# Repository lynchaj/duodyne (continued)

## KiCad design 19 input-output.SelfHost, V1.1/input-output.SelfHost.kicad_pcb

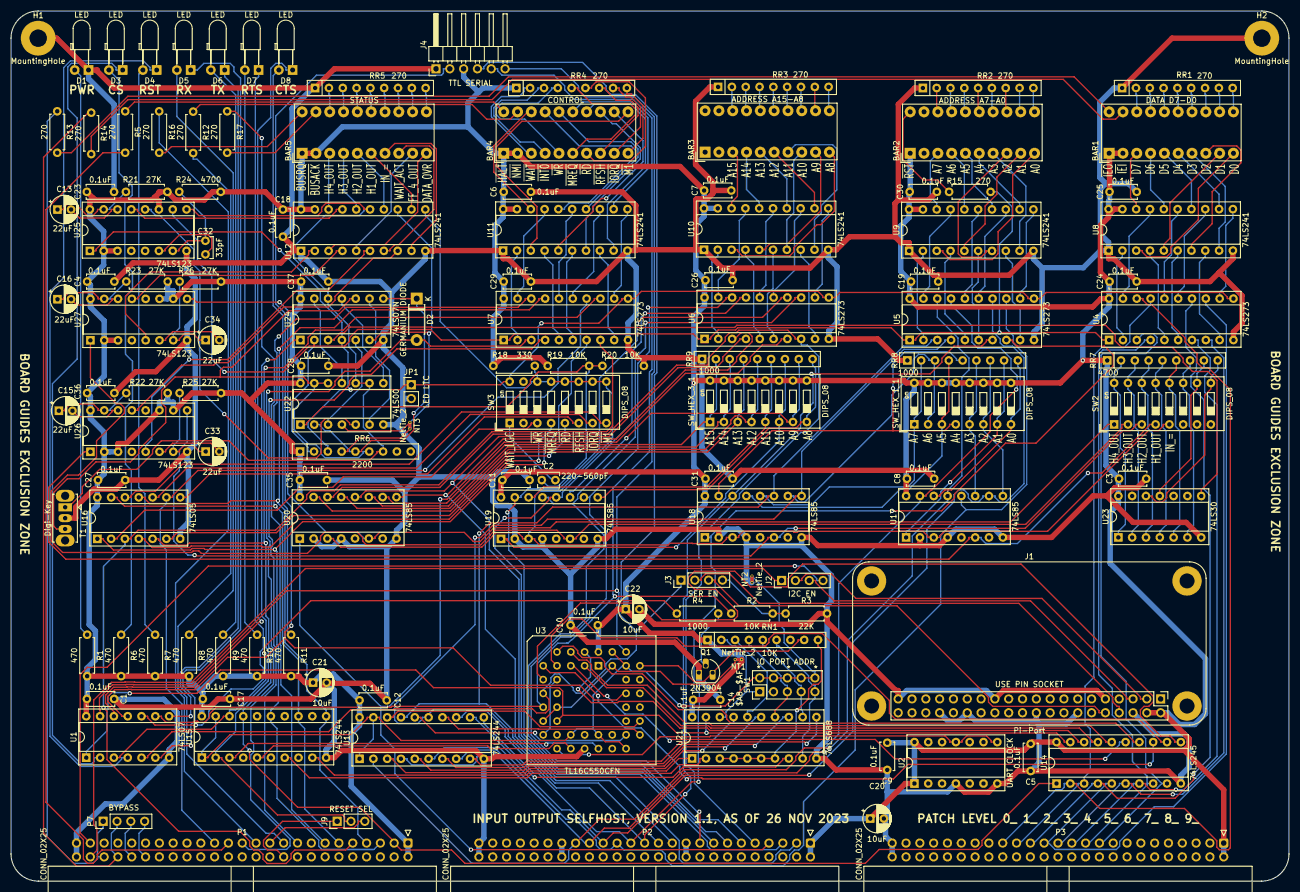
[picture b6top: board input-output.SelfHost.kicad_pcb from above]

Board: 2 copper layers, 235.0 x 160.0 mm, 135 parts (0 on the bottom side), 291 nets.

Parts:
BAR1: DATA D7-D0; HDSP-48xx
BAR2: ADDRESS A7-A0; HDSP-48xx
BAR3: ADDRESS A15-A8; HDSP-48xx
BAR4: CONTROL; HDSP-48xx
BAR5: STATUS; HDSP-48xx
C1, C3, C4, C5, C6, C7, C8, C9, C10, C11, C12, C14, C17, C18, C19, C23, C24, C25, C26, C27, C28, C29, C30, C31, C35, C36, C37: 0.1uF; C_Disc_D5.0mm_W2.5mm_P5.00mm
C2: 220-560pF; C_Disc_D3.8mm_W2.6mm_P2.50mm
C13, C15, C16, C33, C34: 22uF; CP_Radial_D5.0mm_P2.50mm
C20, C21, C22: 10uF; CP_Radial_D5.0mm_P2.50mm
C32: 33pF; C_Disc_D3.8mm_W2.6mm_P2.50mm
D1, D3, D4, D5, D6, D7, D8: LED; LED_D3.0mm_Horizontal_O3.81mm_Z2.0mm
D2: GERMANIUM DIODE; D_DO-41_SOD81_P7.62mm_Horizontal
H1, H2: MountingHole; MountingHole_3.2mm_M3_Pad
J1: Pi-Port
J2: I2C EN; PinHeader_1x04_P2.54mm_Vertical
J3: SER EN; PinHeader_1x04_P2.54mm_Vertical
J4: TTL SERIAL; PinHeader_1x06_P2.54mm_Horizontal
J9: RESET SEL; PinHeader_1x03_P2.54mm_Vertical
JP1: LED LTC; PinHeader_1x02_P2.54mm_Vertical
NT1, NT2, NT3: NetTie_2; NetTie-2_THT_Pad0.3mm
P1, P2, P3: CONN_02X25; IDC-Header_2x25_P2.54mm_Horizontal
P7: BYPASS; PinHeader_1x04_P2.54mm_Vertical
Q1: 2N3904; TO-92_HandSolder
R1, R6, R7, R8, R9, R10, R11: 470; R_Axial_DIN0207_L6.3mm_D2.5mm_P7.62mm_Horizontal
R2, R19, R20: 10K; R_Axial_DIN0207_L6.3mm_D2.5mm_P7.62mm_Horizontal
R3: 22K; R_Axial_DIN0207_L6.3mm_D2.5mm_P7.62mm_Horizontal
R4: 1000; R_Axial_DIN0207_L6.3mm_D2.5mm_P7.62mm_Horizontal
R5, R12, R13, R14, R15, R16, R17: 270; R_Axial_DIN0207_L6.3mm_D2.5mm_P7.62mm_Horizontal
R18: 330; R_Axial_DIN0207_L6.3mm_D2.5mm_P7.62mm_Horizontal
R21, R22, R23, R25, R26: 27K; R_Axial_DIN0207_L6.3mm_D2.5mm_P7.62mm_Horizontal
R24: 4700; R_Axial_DIN0207_L6.3mm_D2.5mm_P7.62mm_Horizontal
RN1: 10K; R_Array_SIP9
RR1, RR2, RR3, RR4, RR5: 270; R_Array_SIP9
RR6: 2200; R_Array_SIP9
RR7: 4700; R_Array_SIP9
RR8, RR9: 1000; R_Array_SIP9
SW1: IO PORT ADDR; PinHeader_2x05_P2.54mm_Vertical
SW2, SW3: DIPS_08; SW_DIP_SPSTx08_Slide_9.78x22.5mm_W7.62mm_P2.54mm
SW_HEX_1_1, SW_HEX_3_1: DIPS_08; SW_DIP_SPSTx08_Slide_9.78x22.5mm_W7.62mm_P2.54mm
T1: Digi-Key; SW_Slide_1P2T_CK_OS102011MS2Q
U1: 74LS07; DIP-14_W7.62mm_Socket
U2: UART CLOCK; DIP-14_W7.62mm_Socket
U3: TL16C550CFN; PLCC-44_THT-Socket
U4, U5, U6, U7: 74LS273; DIP-20_W7.62mm_Socket
U8, U9, U10, U11, U12: 74LS241; DIP-20_W7.62mm_Socket
U13, U15: 74LS244; DIP-20_W7.62mm_Socket
U14: 74LS245; DIP-20_W7.62mm_Socket
U16: 74LS05; DIP-14_W7.62mm_Socket
U17, U18, U19, U20: 74LS85; DIP-16_W7.62mm_Socket
U21: 74LS688; DIP-20_W7.62mm_Socket
U22: 74LS00; DIP-14_W7.62mm_Socket
U23: 74LS30; DIP-14_W7.62mm_Socket
U24: 74LS07N; DIP-14_W7.62mm_Socket
U25, U26, U27: 74LS123; DIP-16_W7.62mm_Socket

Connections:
+12V: P2.19, P2.20
-12V: P2.37, P2.38
/BusMonitor/DATA_OVER: U12.17 (I3b), U25.13 (Q)
/BusMonitor/FF_1_OUT: NT3.2, RR6.4 (R3)
/BusMonitor/FF_2_OUT: D2.1 (K), RR6.5 (R4), U22.2, U24.8
/BusMonitor/FF_3_OUT: RR6.6 (R5), T1.3 (C), U22.12, U22.13, U24.10
/BusMonitor/FF_4_OUT: RR6.7 (R6), T1.1 (A), U12.15 (I2b), U22.9, U22.10, U24.12, U25.9 (A)
/BusMonitor/H1_LED: U12.8 (I3a), U26.13 (Q)
/BusMonitor/H1_OUT_=: SW2.4, U17.6 (Oa=b), U26.1 (A)
/BusMonitor/H2_LED: U12.6 (I2a), U26.5 (Q)
/BusMonitor/H2_OUT_=: SW2.3, U18.6 (Oa=b), U26.9 (A)
/BusMonitor/H3_LED: U12.4 (I1a), U27.13 (Q)
/BusMonitor/H3_OUT_=: SW2.2, U19.6 (Oa=b), U27.1 (A)
/BusMonitor/H4_LED: U12.2 (I0a), U27.5 (Q)
/BusMonitor/H4_OUT_=: SW2.1, U20.6 (Oa=b), U27.9 (A)
/BusMonitor/H_A0: RR8.9 (R8), SW_HEX_1_1.8, U17.14 (B2)
/BusMonitor/H_A1: RR8.8 (R7), SW_HEX_1_1.7, U17.1 (B3)
/BusMonitor/H_A2: RR8.7 (R6), SW_HEX_1_1.6, U17.9 (B0)
/BusMonitor/H_A3: RR8.6 (R5), SW_HEX_1_1.5, U17.11 (B1)
/BusMonitor/H_A4: RR8.5 (R4), SW_HEX_1_1.4, U18.15 (A3)
/BusMonitor/H_A5: RR8.4 (R3), SW_HEX_1_1.3, U18.13 (A2)
/BusMonitor/H_A6: RR8.3 (R2), SW_HEX_1_1.2, U18.10 (A0)
/BusMonitor/H_A7: RR8.2 (R1), SW_HEX_1_1.1, U18.12 (A1)
/BusMonitor/H_A8: RR9.9 (R8), SW_HEX_3_1.8, U19.9 (B0)
/BusMonitor/H_A9: RR9.8 (R7), SW_HEX_3_1.7, U19.11 (B1)
/BusMonitor/H_A10: RR9.7 (R6), SW_HEX_3_1.6, U19.1 (B3)
/BusMonitor/H_A11: RR9.6 (R5), SW_HEX_3_1.5, U19.14 (B2)
/BusMonitor/H_A12: RR9.5 (R4), SW_HEX_3_1.4, U20.13 (A2)
/BusMonitor/H_A13: RR9.4 (R3), SW_HEX_3_1.3, U20.15 (A3)
/BusMonitor/H_A14: RR9.3 (R2), SW_HEX_3_1.2, U20.11 (B1)
/BusMonitor/H_A15: RR9.2 (R1), SW_HEX_3_1.1, U20.10 (A0)
/BusMonitor/IN_=: R18.2, SW2.5, SW3.9, SW3.10, SW3.11, SW3.12, SW3.13, SW3.14, U12.11 (I0b), U17.3 (Ia=b), U18.3 (Ia=b), U19.3 (Ia=b), U20.3 (Ia=b)
/BusMonitor/LED_LATCH: JP1.1 (A), RR6.3 (R2), SW3.16, U4.11 (Cp), U5.11 (Cp), U6.11 (Cp), U7.11 (Cp), U24.4, U25.1 (A)
/BusMonitor/MAS_RESET: R15.2, RR6.2 (R1), U4.1 (~Mr), U5.1 (~Mr), U6.1 (~Mr), U7.1 (~Mr), U24.2, U25.10 (B)
/BusMonitor/S2_1: RR7.2 (R1), SW2.16, U23.1
/BusMonitor/S2_2: RR7.3 (R2), SW2.15, U23.2
/BusMonitor/S2_3: RR7.4 (R3), SW2.14, U23.3
/BusMonitor/S2_4: RR7.5 (R4), SW2.13, U23.4
/BusMonitor/S2_5: RR7.6 (R5), SW2.12, U23.5
/BusMonitor/S2_6: RR7.7 (R6), SW2.11, U23.6
/BusMonitor/S2_7: RR7.8 (R7), SW2.10, U23.11
/BusMonitor/S2_8: RR7.9 (R8), SW2.9, U23.12
/BusMonitor/WAIT_ACTIVE: NT3.1, U12.13 (I1b), U22.4, U24.6
/BusMonitor/WAIT_FF: U22.5, U25.12 (~Q)
/BusMonitor/WAIT_LOGIC: C2.1, R19.2, R20.1, U22.1
A0: P2.35, U5.18 (D7), U13.2 (I0a), U17.13 (A2)
A1: P2.33, U5.17 (D6), U13.4 (I1a), U17.15 (A3)
A2: P2.31, U5.14 (D5), U13.6 (I2a), U17.10 (A0)
A3: P2.29, U5.13 (D4), U13.8 (I3a), U17.12 (A1)
A4: P2.27, U5.8 (D3), U13.11 (I0b), U18.1 (B3)
A5: P2.25, U5.7 (D2), U13.13 (I1b), U18.14 (B2)
A6: P2.23, U5.4 (D1), U13.15 (I2b), U18.9 (B0)
A7: P2.21, U5.3 (D0), U13.17 (I3b), U18.11 (B1)
A8: P2.17, U6.18 (D7), U19.10 (A0)
A9: P2.15, U6.17 (D6), U19.12 (A1)
A10: P2.13, U6.14 (D5), U19.15 (A3)
A11: P2.11, U6.13 (D4), U19.13 (A2)
A12: P2.9, U6.8 (D3), U20.14 (B2)
A13: P2.7, U6.7 (D2), U20.1 (B3)
A14: P2.5, U6.4 (D1), U20.12 (A1)
A15: P2.3, U6.3 (D0), U20.9 (B0)
D0: P3.33, U4.18 (D7), U14.2 (A0)
D1: P3.31, U4.17 (D6), U14.3 (A1)
D2: P3.29, U4.14 (D5), U14.4 (A2)
D3: P3.27, U4.13 (D4), U14.5 (A3)
D4: P3.25, U4.8 (D3), U14.6 (A4)
D5: P3.23, U4.7 (D2), U14.7 (A5)
D6: P3.21, U4.4 (D1), U14.8 (A6)
D7: P3.19, U4.3 (D0), U14.9 (A7)
GND: C1.2, C3.2, C4.2, C5.2, C6.2, C7.2, C8.2, C9.2, C10.2, C11.2, C12.2, C14.2, C17.2, C18.2, C19.2, C20.2, C21.2, C22.2, C23.2, C24.2, C25.2, C26.2, C27.2, C28.2, C29.2, C30.2, C31.2, C35.2, C36.2, C37.2, D1.1 (K), H1.1, H2.1, J1.6, J1.9, J1.14, J1.20, J1.25, J1.30, J1.34, J1.39, J4.1, JP1.2 (B), NT2.1, P1.49, P1.50, P2.49, P2.50, P3.49, P3.50, Q1.1 (E), R3.2, R20.2, RR1.1 (common), RR2.1 (common), RR3.1 (common), RR5.1 (common), RR8.1 (common), RR9.1 (common), T1.2 (B), U1.7 (GND), U2.4, U2.7, U3.22 (GND), U4.10 (GND), U5.10 (GND), U6.10 (GND), U7.10 (GND), U8.1 (OEa), U8.10 (GND), U9.1 (OEa), U9.10 (GND), U10.1 (OEa), U10.10 (GND), U11.1 (OEa), U11.10 (GND), U12.1 (OEa), U12.10 (GND), U13.10 (GND), U14.10 (GND), U15.10 (GND), U16.7 (GND), U17.2 (Ia<b), U17.4 (Ia>b), U17.8 (GND), U18.2 (Ia<b), U18.4 (Ia>b), U18.8 (GND), U19.2 (Ia<b), U19.4 (Ia>b), U19.8 (GND), U20.2 (Ia<b), U20.4 (Ia>b), U20.8 (GND), U21.10 (GND), U22.7 (GND), U23.7 (GND), U24.7 (GND), U25.8 (GND), U26.8 (GND), U27.8 (GND)
I2C_SCL: J2.4, P1.47
I2C_SDA: J2.1, P1.48
unnamed: BAR1.3 (A), U8.18 (O0a)
unnamed: BAR1.4 (A), U8.16 (O1a)
unnamed: BAR1.5 (A), U8.14 (O2a)
unnamed: BAR1.6 (A), U8.12 (O3a)
unnamed: BAR1.7 (A), U8.9 (O0b)
unnamed: BAR1.8 (A), U8.7 (O1b)
unnamed: BAR1.9 (A), U8.5 (O2b)
unnamed: BAR1.10 (A), U8.3 (O3b)
unnamed: BAR1.11 (K), RR1.9 (R8)
unnamed: BAR1.12 (K), RR1.8 (R7)
unnamed: BAR1.13 (K), RR1.7 (R6)
unnamed: BAR1.14 (K), RR1.6 (R5)
unnamed: BAR1.15 (K), RR1.5 (R4)
unnamed: BAR1.16 (K), RR1.4 (R3)
unnamed: BAR1.17 (K), RR1.3 (R2)
unnamed: BAR1.18 (K), RR1.2 (R1)
unnamed: BAR1.19 (K), R14.2
unnamed: BAR1.20 (K), R13.2
unnamed: BAR2.3 (A), U9.18 (O0a)
unnamed: BAR2.4 (A), U9.16 (O1a)
unnamed: BAR2.5 (A), U9.14 (O2a)
unnamed: BAR2.6 (A), U9.12 (O3a)
unnamed: BAR2.7 (A), U9.9 (O0b)
unnamed: BAR2.8 (A), U9.7 (O1b)
unnamed: BAR2.9 (A), U9.5 (O2b)
unnamed: BAR2.10 (A), U9.3 (O3b)
unnamed: BAR2.11 (K), RR2.9 (R8)
unnamed: BAR2.12 (K), RR2.8 (R7)
unnamed: BAR2.13 (K), RR2.7 (R6)
unnamed: BAR2.14 (K), RR2.6 (R5)
unnamed: BAR2.15 (K), RR2.5 (R4)
unnamed: BAR2.16 (K), RR2.4 (R3)
unnamed: BAR2.17 (K), RR2.3 (R2)
unnamed: BAR2.18 (K), RR2.2 (R1)
unnamed: BAR2.20 (K), R15.1
unnamed: BAR3.3 (A), U10.18 (O0a)
unnamed: BAR3.4 (A), U10.16 (O1a)
unnamed: BAR3.5 (A), U10.14 (O2a)
unnamed: BAR3.6 (A), U10.12 (O3a)
unnamed: BAR3.7 (A), U10.9 (O0b)
unnamed: BAR3.8 (A), U10.7 (O1b)
unnamed: BAR3.9 (A), U10.5 (O2b)
unnamed: BAR3.10 (A), U10.3 (O3b)
unnamed: BAR3.11 (K), RR3.9 (R8)
unnamed: BAR3.12 (K), RR3.8 (R7)
unnamed: BAR3.13 (K), RR3.7 (R6)
unnamed: BAR3.14 (K), RR3.6 (R5)
unnamed: BAR3.15 (K), RR3.5 (R4)
unnamed: BAR3.16 (K), RR3.4 (R3)
unnamed: BAR3.17 (K), RR3.3 (R2)
unnamed: BAR3.18 (K), RR3.2 (R1)
unnamed: BAR4.3 (A), RR4.2 (R1)
unnamed: BAR4.4 (A), RR4.3 (R2)
unnamed: BAR4.5 (A), RR4.4 (R3)
unnamed: BAR4.6 (A), RR4.5 (R4)
unnamed: BAR4.7 (A), RR4.6 (R5)
unnamed: BAR4.8 (A), RR4.7 (R6)
unnamed: BAR4.9 (A), RR4.8 (R7)
unnamed: BAR4.10 (A), RR4.9 (R8)
unnamed: BAR4.11 (K), U11.3 (O3b)
unnamed: BAR4.12 (K), U11.5 (O2b)
unnamed: BAR4.13 (K), U11.7 (O1b)
unnamed: BAR4.14 (K), U11.9 (O0b)
unnamed: BAR4.15 (K), U11.12 (O3a)
unnamed: BAR4.16 (K), U11.14 (O2a)
unnamed: BAR4.17 (K), U11.16 (O1a)
unnamed: BAR4.18 (K), U11.18 (O0a)
unnamed: BAR4.19 (K), R12.1
unnamed: BAR4.20 (K), R5.1
unnamed: BAR5.3 (A), U12.18 (O0a)
unnamed: BAR5.4 (A), U12.16 (O1a)
unnamed: BAR5.5 (A), U12.14 (O2a)
unnamed: BAR5.6 (A), U12.12 (O3a)
unnamed: BAR5.7 (A), U12.9 (O0b)
unnamed: BAR5.8 (A), U12.7 (O1b)
unnamed: BAR5.9 (A), U12.5 (O2b)
unnamed: BAR5.10 (A), U12.3 (O3b)
unnamed: BAR5.11 (K), RR5.9 (R8)
unnamed: BAR5.12 (K), RR5.8 (R7)
unnamed: BAR5.13 (K), RR5.7 (R6)
unnamed: BAR5.14 (K), RR5.6 (R5)
unnamed: BAR5.15 (K), RR5.5 (R4)
unnamed: BAR5.16 (K), RR5.4 (R3)
unnamed: BAR5.17 (K), RR5.3 (R2)
unnamed: BAR5.18 (K), RR5.2 (R1)
unnamed: BAR5.19 (K), R17.2
unnamed: BAR5.20 (K), R16.2
unnamed: C2.2, SW3.1
unnamed: C13.1, R21.1, U25.15 (RCext)
unnamed: C13.2, U25.14 (Cext)
unnamed: C15.1, R22.1, U26.15 (RCext)
unnamed: C15.2, U26.14 (Cext)
unnamed: C16.1, R23.1, U27.15 (RCext)
unnamed: C16.2, U27.14 (Cext)
unnamed: C32.1, U25.6 (Cext)
unnamed: C32.2, R24.1, U25.7 (RCext)
unnamed: C33.1, R25.1, U26.7 (RCext)
unnamed: C33.2, U26.6 (Cext)
unnamed: C34.1, R26.1, U27.7 (RCext)
unnamed: C34.2, U27.6 (Cext)
unnamed: D1.2 (A), R1.1
unnamed: D3.1 (K), U1.2
unnamed: D3.2 (A), R6.1
unnamed: D4.1 (K), U1.4
unnamed: D4.2 (A), R7.1
unnamed: D5.1 (K), U1.6
unnamed: D5.2 (A), R8.1
unnamed: D6.1 (K), U1.8
unnamed: D6.2 (A), R9.1
unnamed: D7.1 (K), U1.10
unnamed: D7.2 (A), R10.1
unnamed: D8.1 (K), U1.12
unnamed: D8.2 (A), R11.1
unnamed: J1.3, J2.2
unnamed: J1.5, J2.3
unnamed: J1.8, J3.2
unnamed: J1.10, J3.3
unnamed: Q1.2 (B), R4.2
unnamed: RN1.2 (R1), SW1.1, U21.18 (R7)
unnamed: RN1.3 (R2), SW1.3, U21.16 (R6)
unnamed: RN1.4 (R3), SW1.5, U21.14 (R5)
unnamed: RN1.5 (R4), SW1.7, U21.12 (R4)
unnamed: RN1.6 (R5), SW1.9, U21.9 (R3)
unnamed: RN1.9 (R8), U21.3 (R0), U21.4 (P1), U21.5 (R1), U21.6 (P2), U21.7 (R2)
unnamed: SW3.3, U16.2
unnamed: SW3.4, U16.4
unnamed: SW3.5, U16.6
unnamed: SW3.6, U16.8
unnamed: SW3.7, U16.10
unnamed: SW3.8, U16.12
unnamed: U3.10 (RCLK), U3.17 (~BAUDOUT)
unnamed: U4.2 (Q0), U8.2 (I0a)
unnamed: U4.5 (Q1), U8.4 (I1a)
unnamed: U4.6 (Q2), U8.6 (I2a)
unnamed: U4.9 (Q3), U8.8 (I3a)
unnamed: U4.12 (Q4), U8.11 (I0b)
unnamed: U4.15 (Q5), U8.13 (I1b)
unnamed: U4.16 (Q6), U8.15 (I2b)
unnamed: U4.19 (Q7), U8.17 (I3b)
unnamed: U5.2 (Q0), U9.2 (I0a)
unnamed: U5.5 (Q1), U9.4 (I1a)
unnamed: U5.6 (Q2), U9.6 (I2a)
unnamed: U5.9 (Q3), U9.8 (I3a)
unnamed: U5.12 (Q4), U9.11 (I0b)
unnamed: U5.15 (Q5), U9.13 (I1b)
unnamed: U5.16 (Q6), U9.15 (I2b)
unnamed: U5.19 (Q7), U9.17 (I3b)
unnamed: U6.2 (Q0), U10.2 (I0a)
unnamed: U6.5 (Q1), U10.4 (I1a)
unnamed: U6.6 (Q2), U10.6 (I2a)
unnamed: U6.9 (Q3), U10.8 (I3a)
unnamed: U6.12 (Q4), U10.11 (I0b)
unnamed: U6.15 (Q5), U10.13 (I1b)
unnamed: U6.16 (Q6), U10.15 (I2b)
unnamed: U6.19 (Q7), U10.17 (I3b)
unnamed: U7.2 (Q0), U11.2 (I0a)
unnamed: U7.5 (Q1), U11.4 (I1a)
unnamed: U7.6 (Q2), U11.6 (I2a)
unnamed: U7.9 (Q3), U11.8 (I3a)
unnamed: U7.12 (Q4), U11.11 (I0b)
unnamed: U7.15 (Q5), U11.13 (I1b)
unnamed: U7.16 (Q6), U11.15 (I2b)
unnamed: U7.19 (Q7), U11.17 (I3b)
unnamed: U22.3, U24.5
unnamed: U22.6, U24.9
unnamed: U22.8, U24.11
unnamed: U22.11, U24.13
unnamed: U23.8, U24.3
ONE: NT1.2, U3.14 (CS0), U3.15 (CS1), U3.43 (~RI)
RESET: Q1.3 (C), RN1.8 (R7), U3.39 (MR)
RX-3.3: J3.1, J4.4, U1.5, U3.11 (SIN)
TX: J4.5, R2.1, U1.9, U3.13 (SOUT)
TX-3.3: J3.4, R2.2, R3.1
UART-CLK: U2.8, U2.11, U3.18 (XIN)
VCC: BAR1.1 (A), BAR1.2 (A), BAR2.1 (A), BAR4.1 (A), BAR4.2 (A), BAR5.1 (A), BAR5.2 (A), C1.1, C3.1, C4.1, C5.1, C6.1, C7.1, C8.1, C9.1, C10.1, C11.1, C12.1, C14.1, C17.1, C18.1, C19.1, C20.1, C21.1, C22.1, C23.1, C24.1, C25.1, C26.1, C27.1, C28.1, C29.1, C30.1, C31.1, C35.1, C36.1, C37.1, J1.2, J1.4, J4.3, NT1.1, P1.1, P1.2, P2.1, P2.2, P3.1, P3.2, R1.2, R6.2, R7.2, R8.2, R9.2, R10.2, R11.2, R18.1, R19.1, R21.2, R22.2, R23.2, R24.2, R25.2, R26.2, RN1.1 (common), RR4.1 (common), RR6.1 (common), RR7.1 (common), SW_HEX_1_1.9, SW_HEX_1_1.10, SW_HEX_1_1.11, SW_HEX_1_1.12, SW_HEX_1_1.13, SW_HEX_1_1.14, SW_HEX_1_1.15, SW_HEX_1_1.16, SW_HEX_3_1.9, SW_HEX_3_1.10, SW_HEX_3_1.11, SW_HEX_3_1.12, SW_HEX_3_1.13, SW_HEX_3_1.14, SW_HEX_3_1.15, SW_HEX_3_1.16, U1.14 (VCC), U2.1, U2.14, U3.44 (VCC), U4.20 (VCC), U5.20 (VCC), U6.20 (VCC), U7.20 (VCC), U8.19 (OEb), U8.20 (VCC), U9.19 (OEb), U9.20 (VCC), U10.19 (OEb), U10.20 (VCC), U11.19 (OEb), U11.20 (VCC), U12.19 (OEb), U12.20 (VCC), U13.20 (VCC), U14.20 (VCC), U15.20 (VCC), U16.14 (VCC), U17.16 (VCC), U18.16 (VCC), U19.16 (VCC), U20.16 (VCC), U21.20 (VCC), U22.14 (VCC), U23.14 (VCC), U24.14 (VCC), U25.2 (B), U25.3 (Clr), U25.11 (Clr), U25.16 (VCC), U26.2 (B), U26.3 (Clr), U26.10 (B), U26.11 (Clr), U26.16 (VCC), U27.2 (B), U27.3 (Clr), U27.10 (B), U27.11 (Clr), U27.16 (VCC)
ZERO: NT2.2, SW1.2, SW1.4, SW1.6, SW1.8, SW1.10, U3.21 (WR), U3.25 (RD), U3.28 (~ADS), U3.41 (~DSR), U3.42 (~DCD), U13.1 (OEa), U13.19 (OEb), U15.1 (OEa), U15.19 (OEb)
bA0: U3.31 (A0), U13.18 (O0a)
bA1: U3.30 (A1), U13.16 (O1a)
bA2: U3.29 (A2), U13.14 (O2a)
bA3: U13.12 (O3a), U21.8 (P3)
bA4: U13.9 (O0b), U21.11 (P4)
bA5: U13.7 (O1b), U21.13 (P5)
bA6: U13.5 (O2b), U21.15 (P6)
bA7: U13.3 (O3b), U21.17 (P7)
bD0: U3.2 (D0), U14.18 (B0)
bD1: U3.3 (D1), U14.17 (B1)
bD2: U3.4 (D2), U14.16 (B2)
bD3: U3.5 (D3), U14.15 (B3)
bD4: U3.6 (D4), U14.14 (B4)
bD5: U3.7 (D5), U14.13 (B5)
bD6: U3.8 (D6), U14.12 (B6)
bD7: U3.9 (D7), U14.11 (B7)
~BAI: P1.40, P7.4
~BAO: P1.42, P7.3
~BUSACK: P1.13, R17.1
~BUSRQ: P1.23, R16.1
~CS-UART: U1.1, U3.16 (~CS2), U14.19 (CE), U21.19 (P=R)
~CTS: J4.6, U1.13, U3.40 (~CTS)
~HALT: P1.27, R5.2
~IEI: P1.44, P7.2, R14.1
~IEO: P1.46, P7.1, R13.1
~INT0: P1.17, U7.4 (D1)
~IORQ: P1.7, U7.17 (D6), U15.11 (I0b), U16.11
~M1: P1.11, U7.18 (D7), U15.13 (I1b), U16.13
~MREQ: P1.9, U7.8 (D3), U16.3
~NMI: P1.19, R12.2
~RD: P1.3, U7.13 (D4), U14.1 (A->B), U15.17 (I3b), U16.5
~RESET: J9.2, U15.2 (I0a), U24.1
~RES_IN: J9.1, P1.20
~RES_OUT: J9.3, P1.21
~RFSH: P1.29, U7.14 (D5), U16.9
~RTS: J4.2, U1.11, U3.36 (~RTS)
~WAIT: D2.2 (A), P1.25, U7.3 (D0)
~WR: P1.5, U7.7 (D2), U15.15 (I2b), U16.1
~bIORQ: U15.9 (O0b), U21.1 (G)
~bM1: U15.7 (O1b), U21.2 (P0)
~bRD: U3.24 (~RD), U15.3 (O3b)
~bRESET: R4.1, U1.3, U15.18 (O0a)
~bWR: U3.20 (~WR), U15.5 (O2b)
